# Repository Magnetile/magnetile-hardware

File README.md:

<div align="center">

# Magnetile Hardware

**Open source modular wireless macropad system**

</div>

---

Magnetile is a modular wireless input device. A central hub connects to interchangeable input tiles - mechanical keys, rotary encoders, sliders, display keys - via magnetic pogo pin connectors. The hub presents as a single BLE HID device to the host. Everything is open source.

> **Personal project by a maker in Bavaria, Germany. Not for commercial sale.**

---

## System Overview

Tiles are hot-swappable modules. Each tile has its own small MCU communicating over I²C. The hub aggregates all input and handles the BLE stack. A single LiPo cell in the hub powers the entire system through the pogo pins.

---

## SnapCore Hub Board

The SnapCore is the first hardware in this repository — the nRF52840-based hub PCB.

### Hardware Stack

| Component | Part | Notes |
|-----------|------|-------|
| MCU | Nordic nRF52840 (AQFN-73) | BLE 5, USB, 1MB flash, 256KB RAM |
| LDO | XC6220B331MR-G (Torex, SOT-23-5) | 3.3V, 1A, ~8µA quiescent |
| Battery charger | TP4056 | Single-cell LiPo, ~300mA charge rate |
| USB | USB-C, 5.1kΩ CC pull-downs |  |
| HF crystal | 32 MHz | nRF52840 system clock |
| RTC crystal | 32.768 kHz | Low-power RTC |
| QSPI flash | W25Q128 (16 MB) | Planned for rev 2 |
| Antenna | PCB trace (meander) | SWRA117D reference, tunable RF matching |
| Tile bus | I²C with 4.7kΩ pull-ups | Pogo pin connector |

### PCB Stackup

| Layer | Function |
|-------|----------|
| F.Cu | Components + signals |
| In1.Cu | Solid GND plane |
| In2.Cu | Power distribution + overflow signals |
| B.Cu | Signals |

- Copper pour excluded from antenna area

### Pinout

---

## Tile Architecture

Tiles are designed to be cheap and simple. The hub owns the BLE stack; tiles just report their input state over I²C when polled.

**Tile MCU target:** CH32V003 (RISC-V, I²C slave)

Each tile exposes:
- I²C slave address (configurable per tile type)
- Input state register (key states, encoder delta, slider position)
- Optional: small display framebuffer via I²C (for display tiles)

The pogo pin connector carries: `VCC`, `GND`, `SDA`, `SCL`, and an optional `INT` line for event-driven wake.

Full tile specification in [`docs/connector-pinout.md`](docs/Pinout.svg).

---

## Software

Firmware lives in the companion repository: [magnetile-firmware](https://github.com/magnetile/magnetile-firmware)

| Component | Stack |
|-----------|-------|
| RTOS | Zephyr / Nordic NCS |
| BLE profile | HID over GATT |
| Wireless config | Web Bluetooth API (browser-based) |
| Debug | RTT (Segger J-Link / nRF9160 DK) |
| Hub–tile protocol | I²C polling, CH32V003 slave firmware |

---

## Status

| Milestone | Status |
|-----------|--------|
| Schematic rev 1 | ✅ Complete |
| PCB layout rev 1 | ✅ Complete |
| Fab files (JLCPCB) | 🔄 In progress |
| Rev 1 bring-up | ⏳ Pending |
| Tile hardware | ⏳ Rev 2 |
| Firmware (hub) | 🔄 In progress |
| Tile firmware | ⏳ Rev 2 |
| Web config UI | ⏳ Planned |

---

## Building / Ordering

All design files are in KiCad 9. Fab outputs (Gerbers, BOM, CPL) for JLCPCB are in `snapcore/fab/`.

**Preferred suppliers:** JLCPCB (PCB + assembly), LCSC (components).

This project is designed around JLCPCB's manufacturing ecosystem. If you want to replicate the build, the Gerbers and BOM are ready to upload directly:

[**Order PCBs / PCBA from JLCPCB**](https://jlcpcb.com/?from=mnt)

For managing orders across services - PCB fabrication, assembly, 3D printing, CNC - JLCPCB offers **JLCONE**, a unified desktop platform that consolidates their full manufacturing stack (JLCPCB, JLC3DP, JLCCNC, JLCMC) into one interface. You can upload files, place orders, and track shipments across all services in one place. The desktop version includes a coupon bundle covering various services and shipping.

[**Download JLCONE**](https://jlcpcb.com/download?from=mnt)

---

## Acknowledgements

This project's prototype run is supported by **[JLCPCB](https://jlcpcb.com/?from=mnt)**. Their PCB fabrication and SMT assembly service makes iterating on dense, complex boards like the SnapCore genuinely accessible for independent open source hardware projects.

---

## License

MIT - see [`LICENSE`](LICENSE).

---

## Contributing

This is a personal project in active development. Issues and suggestions are welcome. See [`CONTRIBUTING.md`](CONTRIBUTING.md) before opening a pull request.

---

<div align="center">
<sub>Made in Bavaria · nRF52840 · KiCad · Zephyr</sub>
</div>

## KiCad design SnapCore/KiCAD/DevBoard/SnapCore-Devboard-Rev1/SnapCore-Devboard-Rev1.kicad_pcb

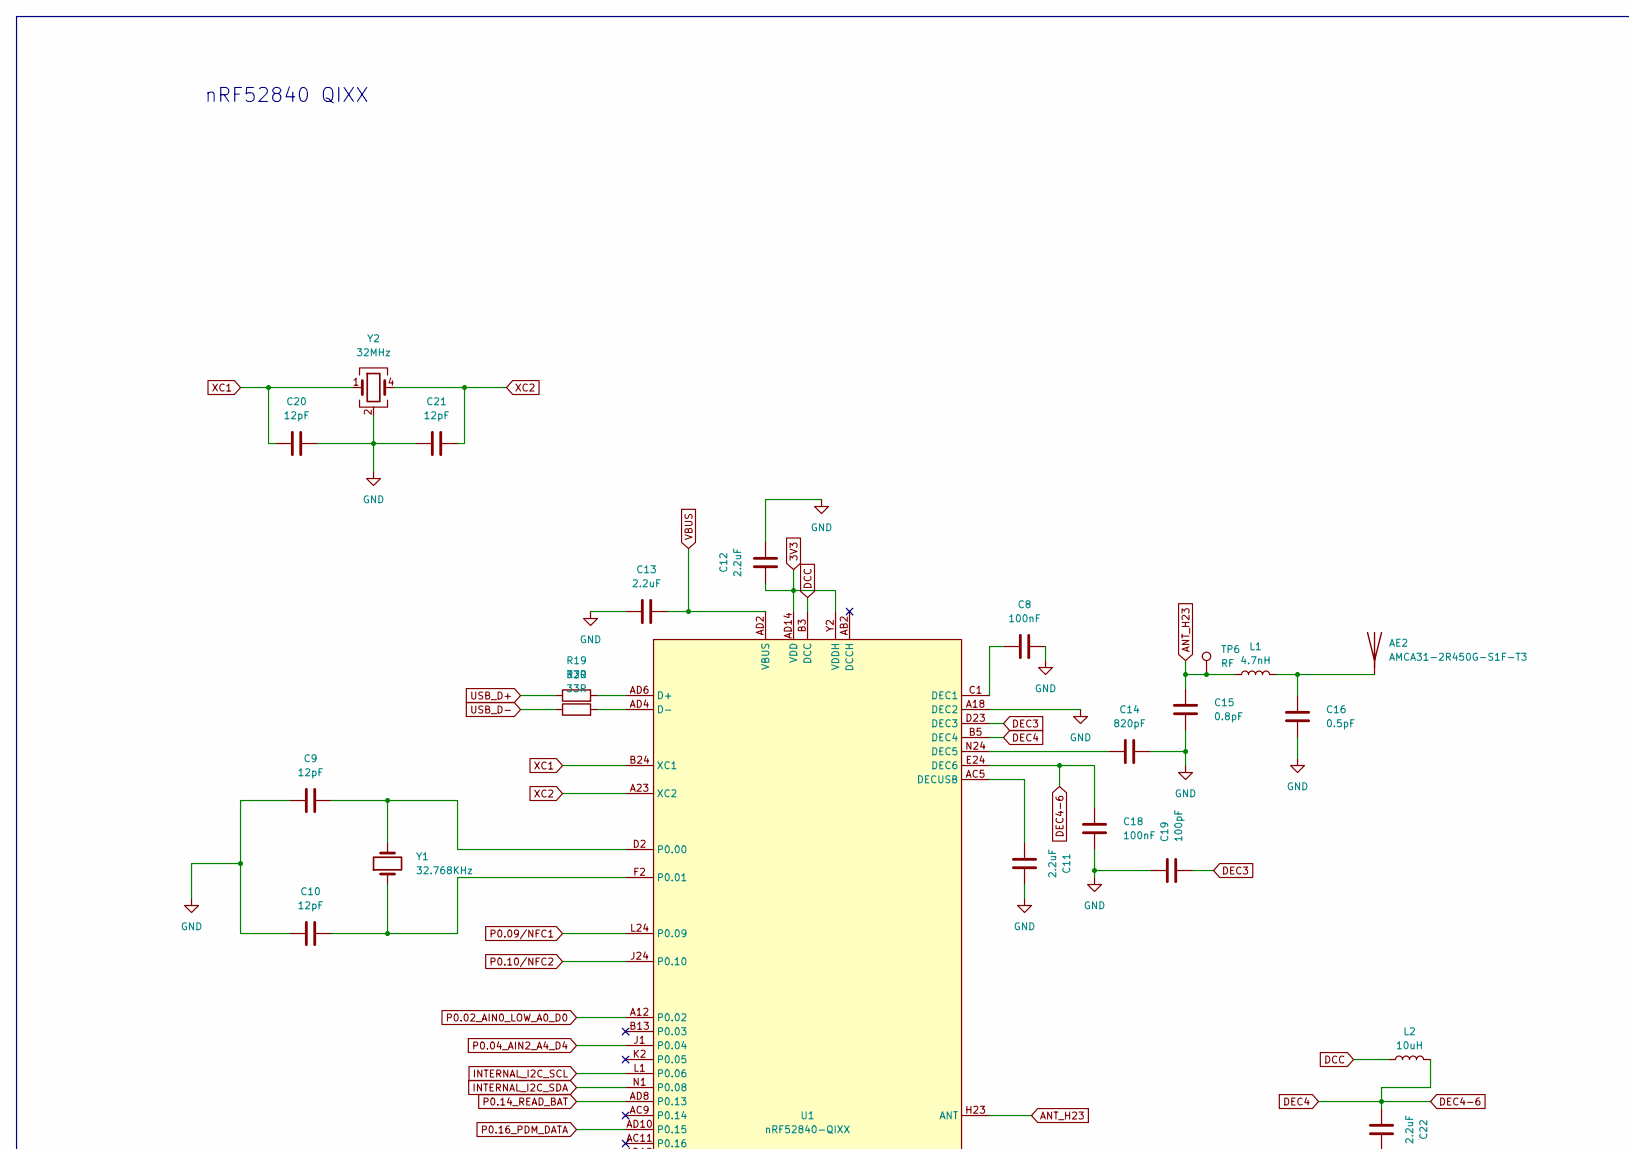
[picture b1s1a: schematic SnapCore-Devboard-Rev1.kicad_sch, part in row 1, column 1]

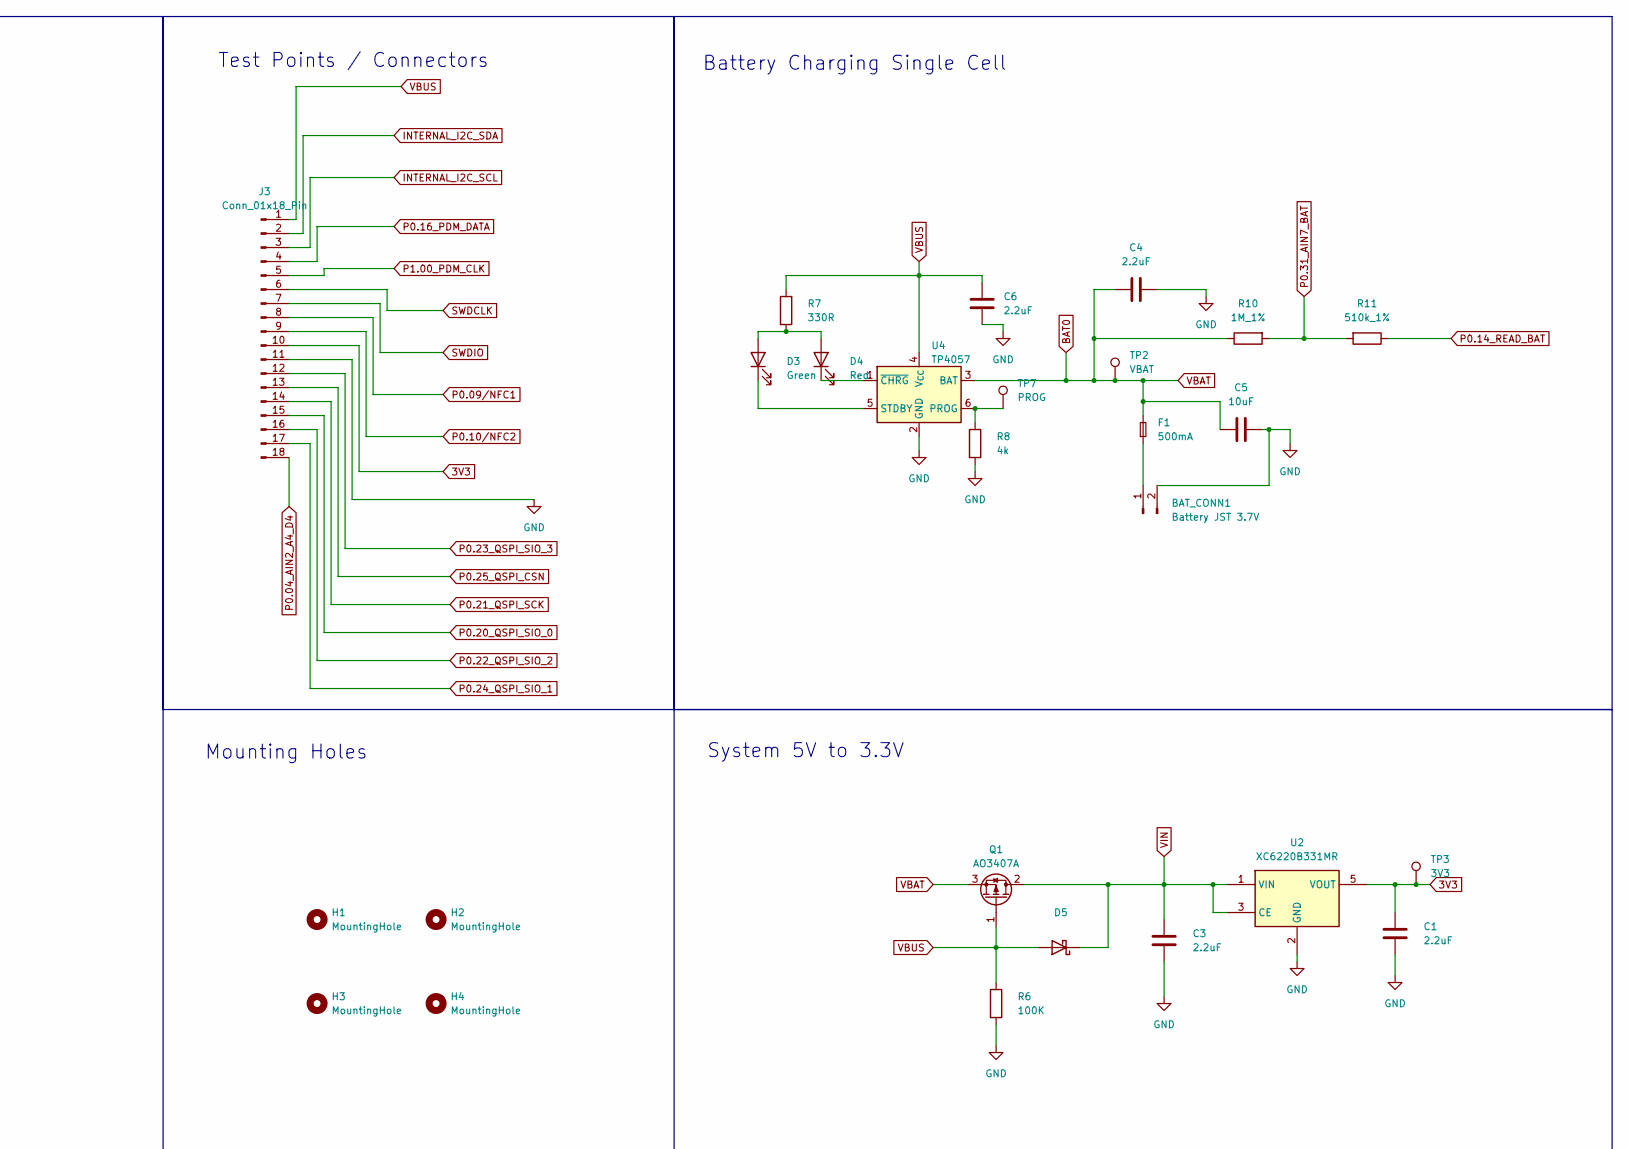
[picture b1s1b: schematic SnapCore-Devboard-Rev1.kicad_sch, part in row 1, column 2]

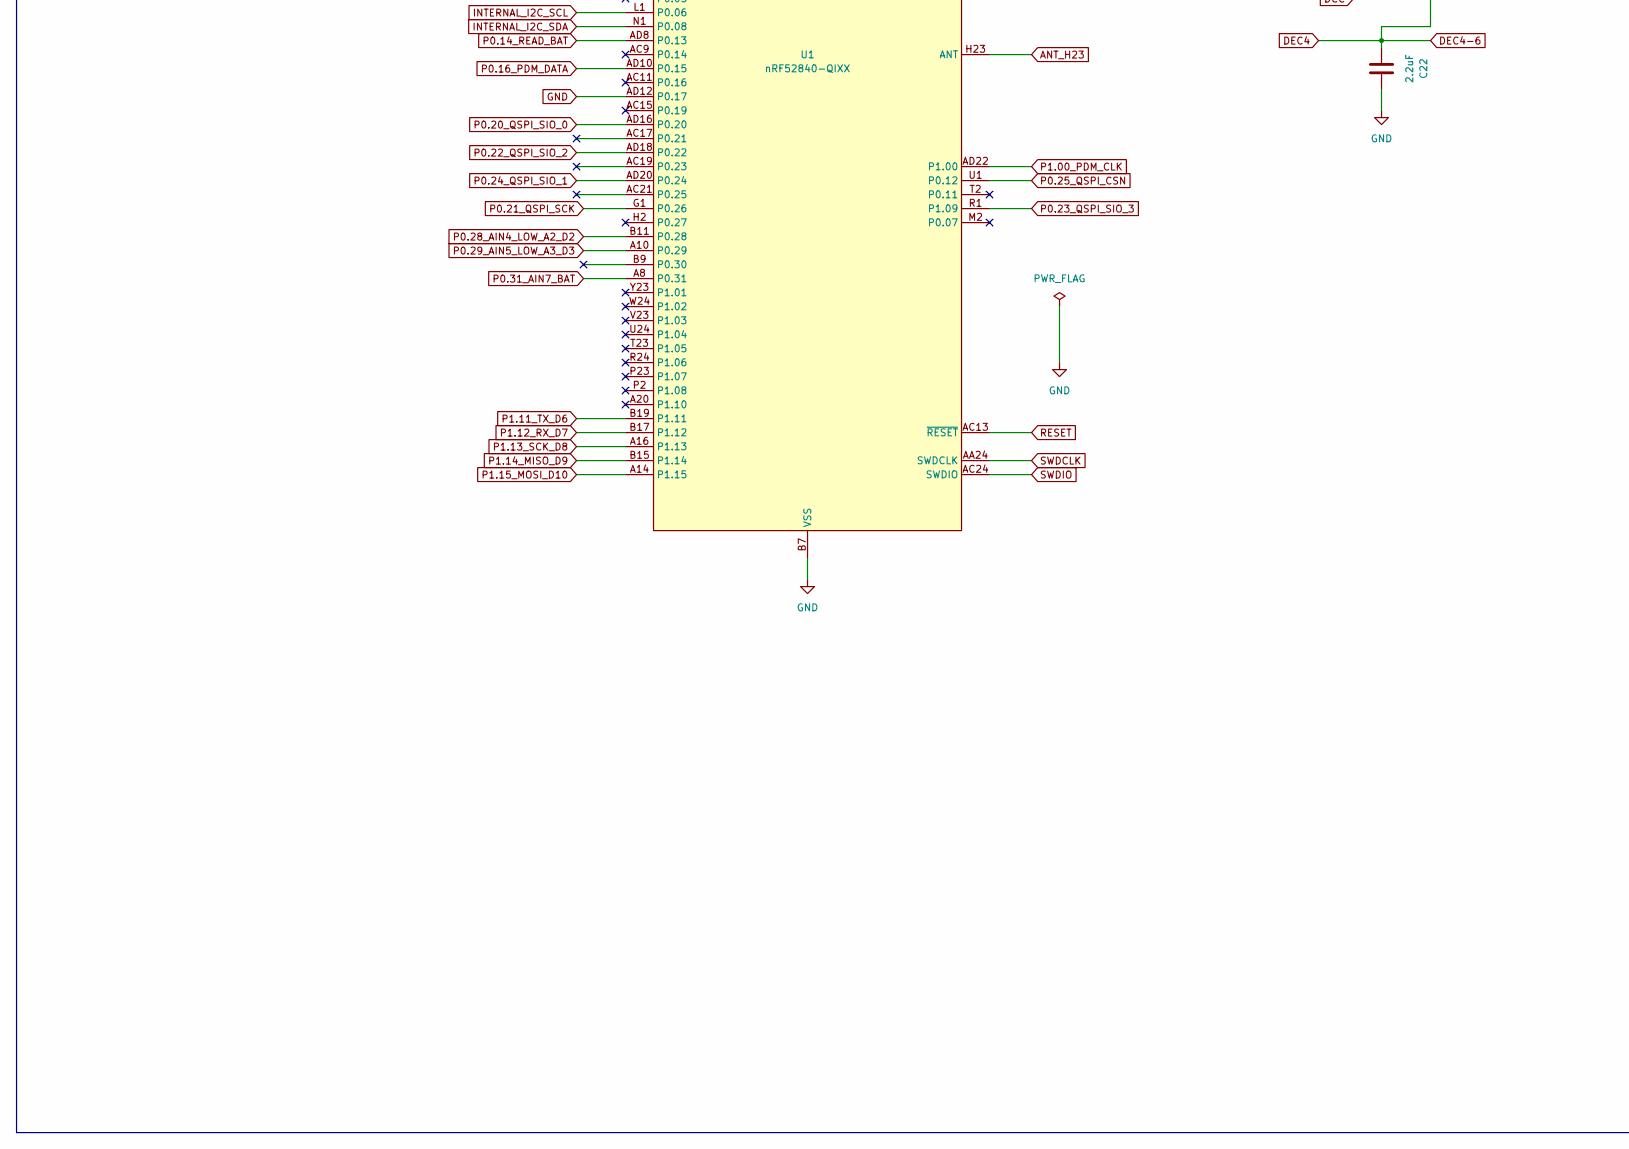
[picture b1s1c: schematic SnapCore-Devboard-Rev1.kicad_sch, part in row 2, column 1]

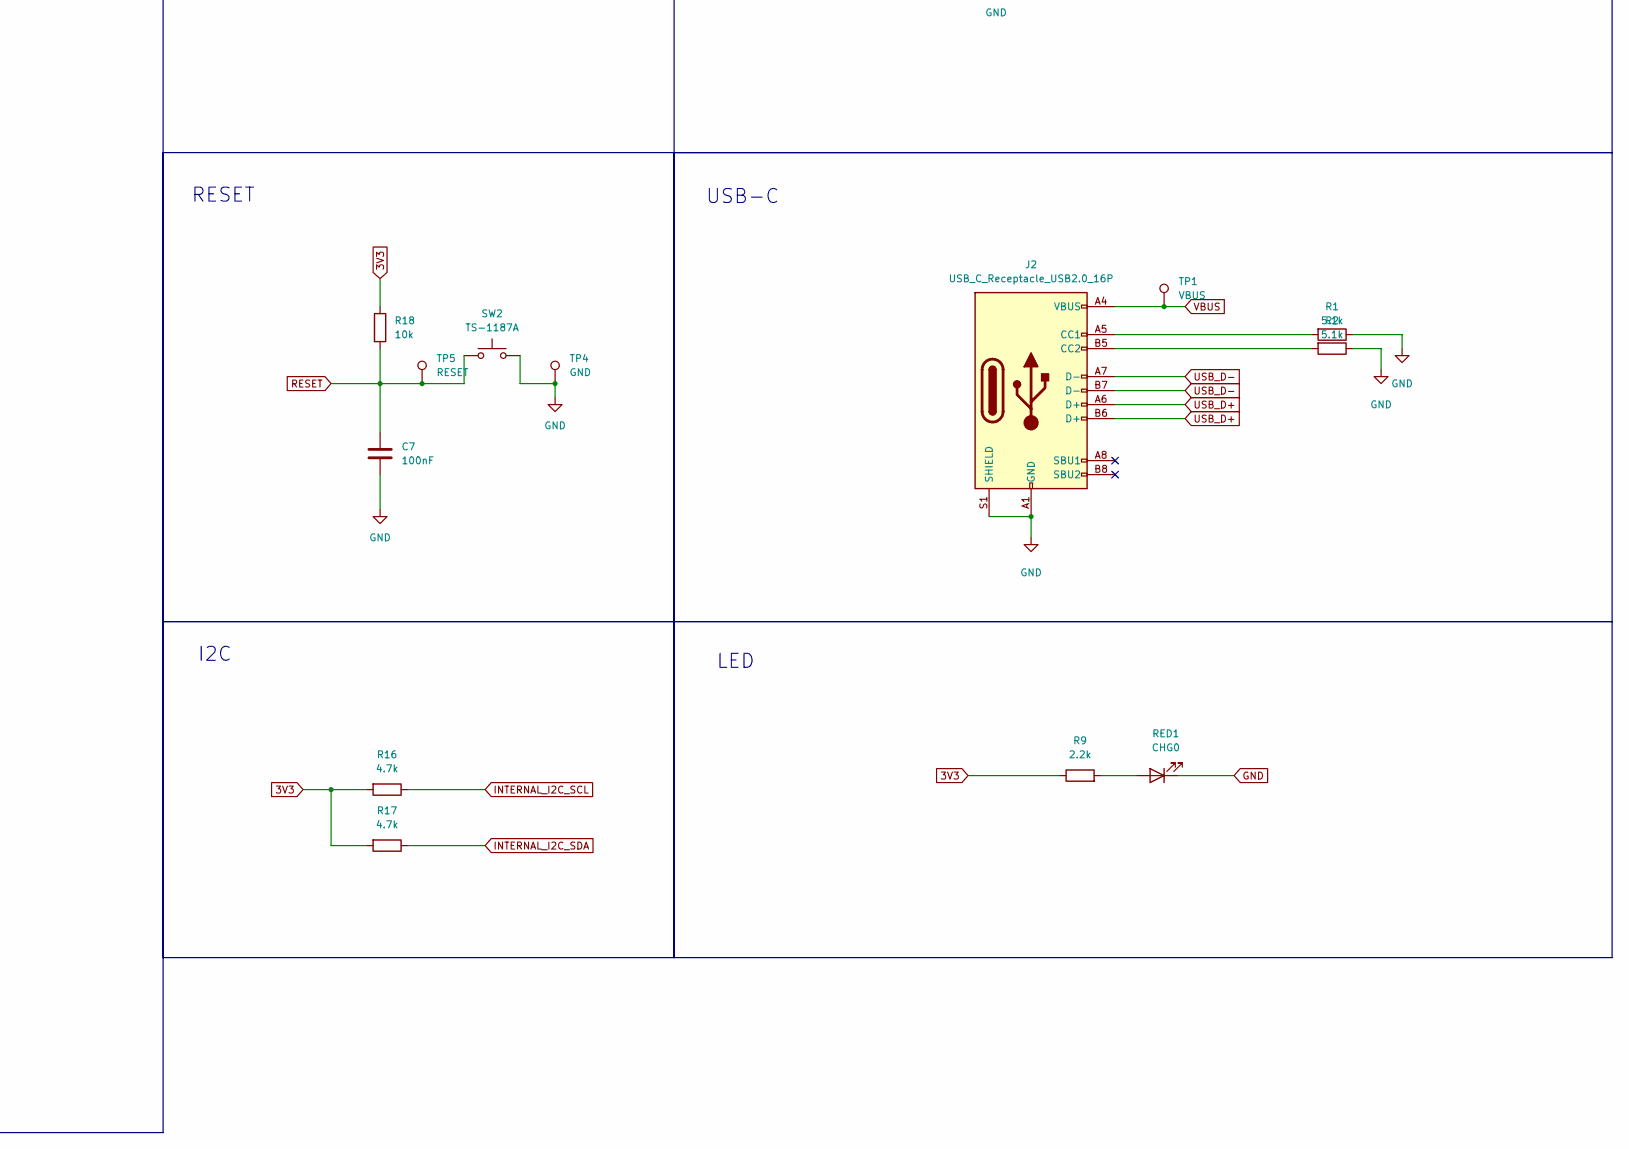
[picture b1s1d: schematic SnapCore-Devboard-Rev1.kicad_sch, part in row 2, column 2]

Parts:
AE2: AMCA31-2R450G-S1F-T3; XDCR_AMCA31-2R450G-S1F-T3
BAT_CONN1: Battery JST 3.7V; JST_EH_B2B-EH-A_1x02_P2.50mm_Vertical
C1, C3, C13, C22: 2.2uF; C_0402_1005Metric
C4: 2.2uF; C_0805_2012Metric
C5: 10uF; C_0402_1005Metric
C6, C11, C12: 2.2uF; C_0603_1608Metric
C7: 100nF; C_0805_2012Metric
C8: 100nF; C_0402_1005Metric
C9, C10, C20, C21: 12pF; C_0402_1005Metric
C14: 820pF; C_0402_1005Metric
C15: 0.8pF; C_0402_1005Metric
C16: 0.5pF; C_0402_1005Metric
C18: 100nF; C_0603_1608Metric
C19: 100pF; C_0402_1005Metric
D3: Green; LED_0805_2012Metric
D4: Red; LED_0805_2012Metric
D5: SDM20U40-7, 40V;250mA; D_SOD-523
F1: 500mA; Fuse_1206_3216Metric
H1, H2, H3, H4: MountingHole; MountingHole_2.2mm_M2_ISO7380_Pad
J2: USB_C_Receptacle_USB2.0_16P; USB_C_Receptacle_GCT_USB4105-xx-A_16P_TopMnt_Horizontal
J3: Conn_01x18_Pin; PinHeader_1x18_P1.27mm_Vertical
L1: 4.7nH; L_0402_1005Metric
L2: 10uH; L_0402_1005Metric
Q1: AO3407A; SOT-23
R1, R2: 5.1k; R_0402_1005Metric
R6: 100K; R_0402_1005Metric
R7: 330R; R_0603_1608Metric
R8: 4k; R_0603_1608Metric
R9: 2.2k; R_0402_1005Metric
R10: 1M_1%; R_0603_1608Metric
R11: 510k_1%; R_0603_1608Metric
R16, R17: 4.7k; R_0402_1005Metric
R18: 10k; R_0402_1005Metric
R19, R20: 33R; R_0402_1005Metric
RED1: CHG0; LED_0603_1608Metric
SW2: TS-1187A; SW_Push_1P1T_XKB_TS-1187A
TP1: VBUS; TestPoint_Pad_D2.0mm
TP2: VBAT; TestPoint_Pad_D2.0mm
TP3: 3V3; TestPoint_Pad_D2.0mm
TP4: GND; TestPoint_Pad_D2.0mm
TP5: RESET; TestPoint_Pad_D2.0mm
TP6: RF; TestPoint_Pad_D2.0mm
TP7: PROG; TestPoint_Pad_D2.0mm
U1: nRF52840-QIXX; Nordic_AQFN-73-1EP_7x7mm_P0.5mm
U2: XC6220B331MR; SOT-23-5
U4: TP4057; TSOT-23-6
Y1: 32.768KHz; Crystal_SMD_3215-2Pin_3.2x1.5mm
Y2: 32MHz; Crystal_SMD_2016-4Pin_2.0x1.6mm

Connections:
3V3: C1.1, C12.2, J3.10, R9.1, R16.2, R17.2, R18.1, TP3.1, U1.A22 (VDD), U1.AD14 (VDD), U1.AD23 (VDD), U1.B1 (VDD), U1.W1 (VDD), U1.Y2 (VDDH), U2.5 (VOUT)
ANT_H23: C15.1, L1.1, TP6.1, U1.H23 (ANT)
BAT0: C4.1, C5.1, F1.2, Q1.3 (S), R10.1, TP2.1, U4.3 (BAT)
DCC: L2.1, U1.B3 (DCC)
DEC3: C19.2, U1.D23 (DEC3)
DEC4: C18.1, C22.2, L2.2, U1.B5 (DEC4), U1.E24 (DEC6)
GND: BAT_CONN1.2, C1.2, C3.2, C4.2, C5.2, C6.1, C7.1, C8.1, C9.2, C10.2, C11.1, C12.1, C13.1, C14.1, C15.2, C16.2, C18.2, C19.1, C20.1, C21.1, C22.1, J2.A1 (GND), J2.A12 (GND), J2.B1 (GND), J2.B12 (GND), J2.S1 (SHIELD), J3.11, R1.1, R2.1, R6.2, R8.2, RED1.1 (K), SW2.2, TP4.1, U1.A18 (DEC2), U1.AD12 (P0.17), U1.B7 (VSS), U1.EP (VSS), U1.F23 (VSS_PA), U2.2 (GND), U4.2 (GND), Y2.2 (G), Y2.3 (G); also elsewhere on the board
INTERNAL_I2C_SCL: J3.3, R16.1, U1.L1 (P0.06)
INTERNAL_I2C_SDA: J3.2, R17.1, U1.N1 (P0.08)
unnamed: AE2.1 (A), C16.1, L1.2
unnamed 10: BAT_CONN1.1, F1.1; also elsewhere on the board
unnamed: D3.2 (A), D4.2 (A), R7.2
unnamed: D3.1 (K), U4.5 (STDBY)
unnamed: D4.1 (K), U4.1 (~CHRG)
unnamed: J2.A5 (CC1), R1.2
unnamed: J2.B5 (CC2), R2.2
unnamed: R9.2, RED1.2 (A)
unnamed: R19.2, U1.AD6 (D+)
unnamed: R20.2, U1.AD4 (D-)
unnamed: C8.2, U1.C1 (DEC1)
unnamed: C14.2, U1.N24 (DEC5)
unnamed: C11.2, U1.AC5 (DECUSB)
unnamed: C9.1, U1.D2 (P0.00), Y1.2
unnamed: C10.1, U1.F2 (P0.01), Y1.1
unnamed: R8.1, TP7.1, U4.6 (PROG)
P0.02_AIN0_LOW_A0_D0: U1.A12 (P0.02)
P0.04_AIN2_A4_D4: J3.18, U1.J1 (P0.04)
P0.09/NFC1: J3.8, U1.L24 (P0.09)
P0.10/NFC2: J3.9, U1.J24 (P0.10)
P0.14_READ_BAT: R11.1, U1.AD8 (P0.13)
P0.16_PDM_DATA: J3.4, U1.AD10 (P0.15)
P0.20_QSPI_SIO_0: J3.15, U1.AD16 (P0.20)
P0.21_QSPI_SCK: J3.14, U1.G1 (P0.26)
P0.22_QSPI_SIO_2: J3.16, U1.AD18 (P0.22)
P0.23_QSPI_SIO_3: J3.12, U1.R1 (P1.09)
P0.24_QSPI_SIO_1: J3.17, U1.AD20 (P0.24)
P0.25_QSPI_CSN: J3.13, U1.U1 (P0.12)
P0.28_AIN4_LOW_A2_D2: U1.B11 (P0.28)
P0.29_AIN5_LOW_A3_D3: U1.A10 (P0.29)
P0.31_AIN7_BAT: R10.2, R11.2, U1.A8 (P0.31)
P1.00_PDM_CLK: J3.5, U1.AD22 (P1.00)
P1.11_TX_D6: U1.B19 (P1.11)
P1.12_RX_D7: U1.B17 (P1.12)
P1.13_SCK_D8: U1.A16 (P1.13)
P1.14_MISO_D9: U1.B15 (P1.14)
P1.15_MOSI_D10: U1.A14 (P1.15)
RESET: C7.2, R18.2, SW2.1, TP5.1, U1.AC13 (~RESET)
SWDCLK: J3.6, U1.AA24 (SWDCLK)
SWDIO: J3.7, U1.AC24 (SWDIO)
USB_D+: J2.A6 (D+), J2.B6 (D+), R19.1
USB_D-: J2.A7 (D-), J2.B7 (D-), R20.1
VBUS: C6.2, C13.2, D5.2 (A), J2.A4 (VBUS), J2.A9 (VBUS), J2.B4 (VBUS), J2.B9 (VBUS), J3.1, Q1.1 (G), R6.1, R7.1, TP1.1, U1.AD2 (VBUS), U4.4 (V_{CC})
VIN: C3.1, D5.1 (K), Q1.2 (D), U2.1 (VIN), U2.3 (CE)
XC1: C20.2, U1.B24 (XC1), Y2.1
XC2: C21.2, U1.A23 (XC2), Y2.4

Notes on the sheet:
USB-C
Test Points / Connectors
LED
Mounting Holes
RESET
I2C
Battery Charging Single Cell
System 5V to 3.3V
nRF52840 QIXX

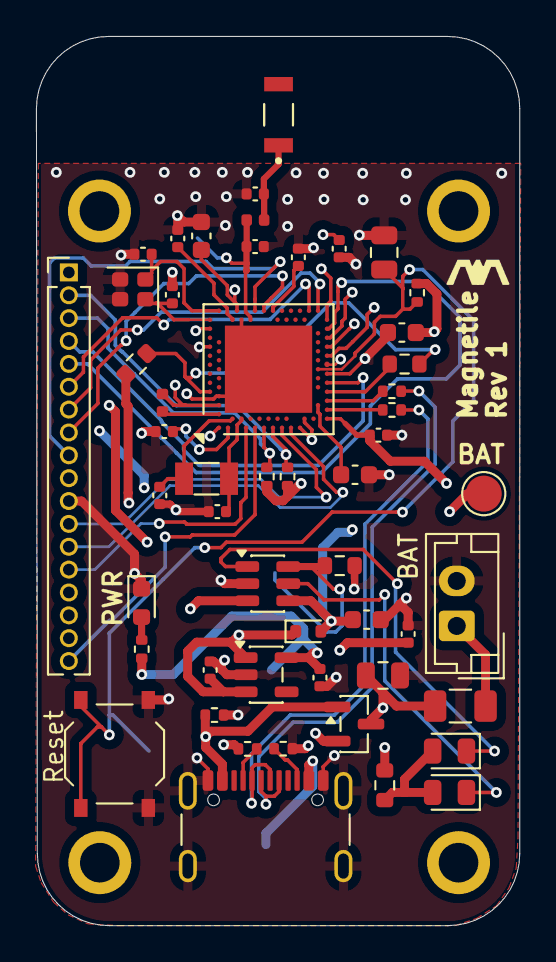
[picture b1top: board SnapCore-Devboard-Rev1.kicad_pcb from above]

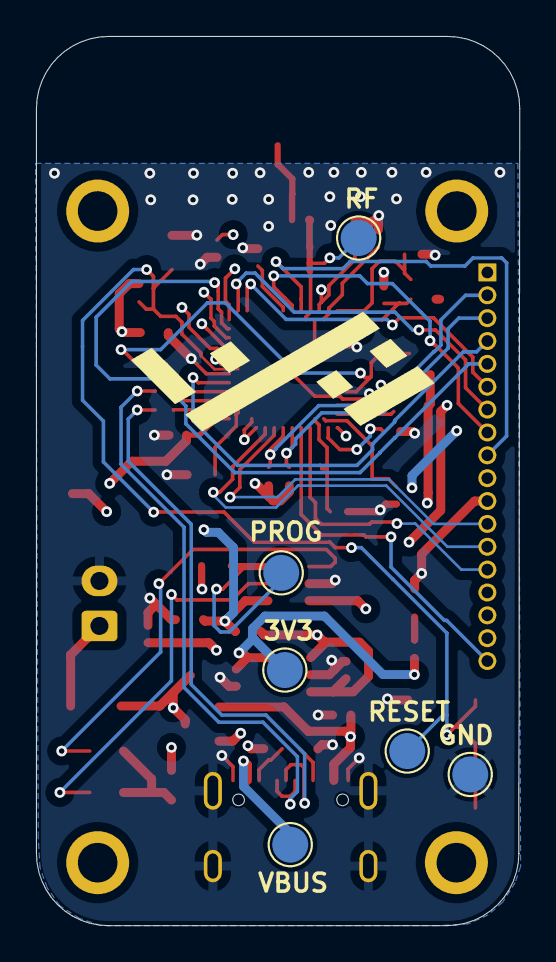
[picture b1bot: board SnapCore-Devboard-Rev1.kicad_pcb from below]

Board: 4 copper layers, 26.8 x 49.4 mm, 62 parts (6 on the bottom side), 47 nets.

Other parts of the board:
BAT: Battery JST 3.7V; JST_EH_B2B-EH-A_1x02_P2.50mm_Vertical

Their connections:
GND: BAT.2; also elsewhere on the board
unnamed 10: BAT.1; also elsewhere on the board

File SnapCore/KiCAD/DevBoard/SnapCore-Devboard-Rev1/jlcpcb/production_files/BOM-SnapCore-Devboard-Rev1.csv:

Comment,Designator,Footprint,LCSC,Quantity
100K,R6,R_0402_1005Metric,C25741,1
100nF,C18,C_0603_1608Metric,C14663,1
100nF,C8,C_0402_1005Metric,C1525,1
100nF,C7,C_0805_2012Metric,C49678,1
100pF,C19,C_0402_1005Metric,C1546,1
10k,R18,R_0402_1005Metric,C25744,1
10uF,C5,C_0402_1005Metric,C15525,1
10uH,L2,L_0402_1005Metric,C48946156,1
12pF,"C10,C20,C21,C9",C_0402_1005Metric,C1547,4
1M_1%,R10,R_0603_1608Metric,C22935,1
2.2k,R9,R_0402_1005Metric,C25879,1
2.2uF,"C1,C13,C22,C3",C_0402_1005Metric,C12530,4
2.2uF,"C11,C12,C6",C_0603_1608Metric,C23630,3
2.2uF,C4,C_0805_2012Metric,C377773,1
32.768KHz,Y1,Crystal_SMD_3215-2Pin_3.2x1.5mm,C32346,1
32MHz,Y2,Crystal_SMD_2016-4Pin_2.0x1.6mm,C187794,1
330R,R7,R_0603_1608Metric,C23138,1
33R,"R19,R20",R_0402_1005Metric,C25105,2
4.7k,"R16,R17",R_0402_1005Metric,C25900,2
4.7nH,L1,L_0402_1005Metric,C13595,1
4k,R8,R_0603_1608Metric,C23018,1
5.1k,"R1,R2",R_0402_1005Metric,C25905,2
500mA,F1,Fuse_1206_3216Metric,C20798,1
510k_1%,R11,R_0603_1608Metric,C23192,1
820pF,C14,C_0402_1005Metric,C1523,1
AMCA31-2R450G-S1F-T3,AE2,XDCR_AMCA31-2R450G-S1F-T3,C3283994,1
AO3407A,Q1,SOT-23,C15155,1
CHG0,RED1,LED_0603_1608Metric,C2286,1
Green,D3,LED_0805_2012Metric,C2297,1
Red,D4,LED_0805_2012Metric,C84256,1
"SDM20U40-7, 40V;250mA",D5,D_SOD-523,C139439,1
TP4057,U4,TSOT-23-6,C440390,1
TS-1187A,SW2,SW_Push_1P1T_XKB_TS-1187A,C318884,1
USB_C_Receptacle_USB2.0_16P,J2,USB_C_Receptacle_GCT_USB4105-xx-A_16P_TopMnt_Horizontal,C136423,1
XC6220B331MR,U2,SOT-23-5,C3040644,1
nRF52840-QIXX,U1,Nordic_AQFN-73-1EP_7x7mm_P0.5mm,C190794,1
Conn_01x18_Pin,J3,PinHeader_1x18_P1.27mm_Vertical,,1
PROG,TP7,TestPoint_Pad_D2.0mm,,1
RF,TP6,TestPoint_Pad_D2.0mm,,1
RESET,TP5,TestPoint_Pad_D2.0mm,,1
GND,TP4,TestPoint_Pad_D2.0mm,,1
3V3,TP3,TestPoint_Pad_D2.0mm,,1
VBAT,TP2,TestPoint_Pad_D2.0mm,,1
VBUS,TP1,TestPoint_Pad_D2.0mm,,1
Battery JST 3.7V,BAT,JST_EH_B2B-EH-A_1x02_P2.50mm_Vertical,,1

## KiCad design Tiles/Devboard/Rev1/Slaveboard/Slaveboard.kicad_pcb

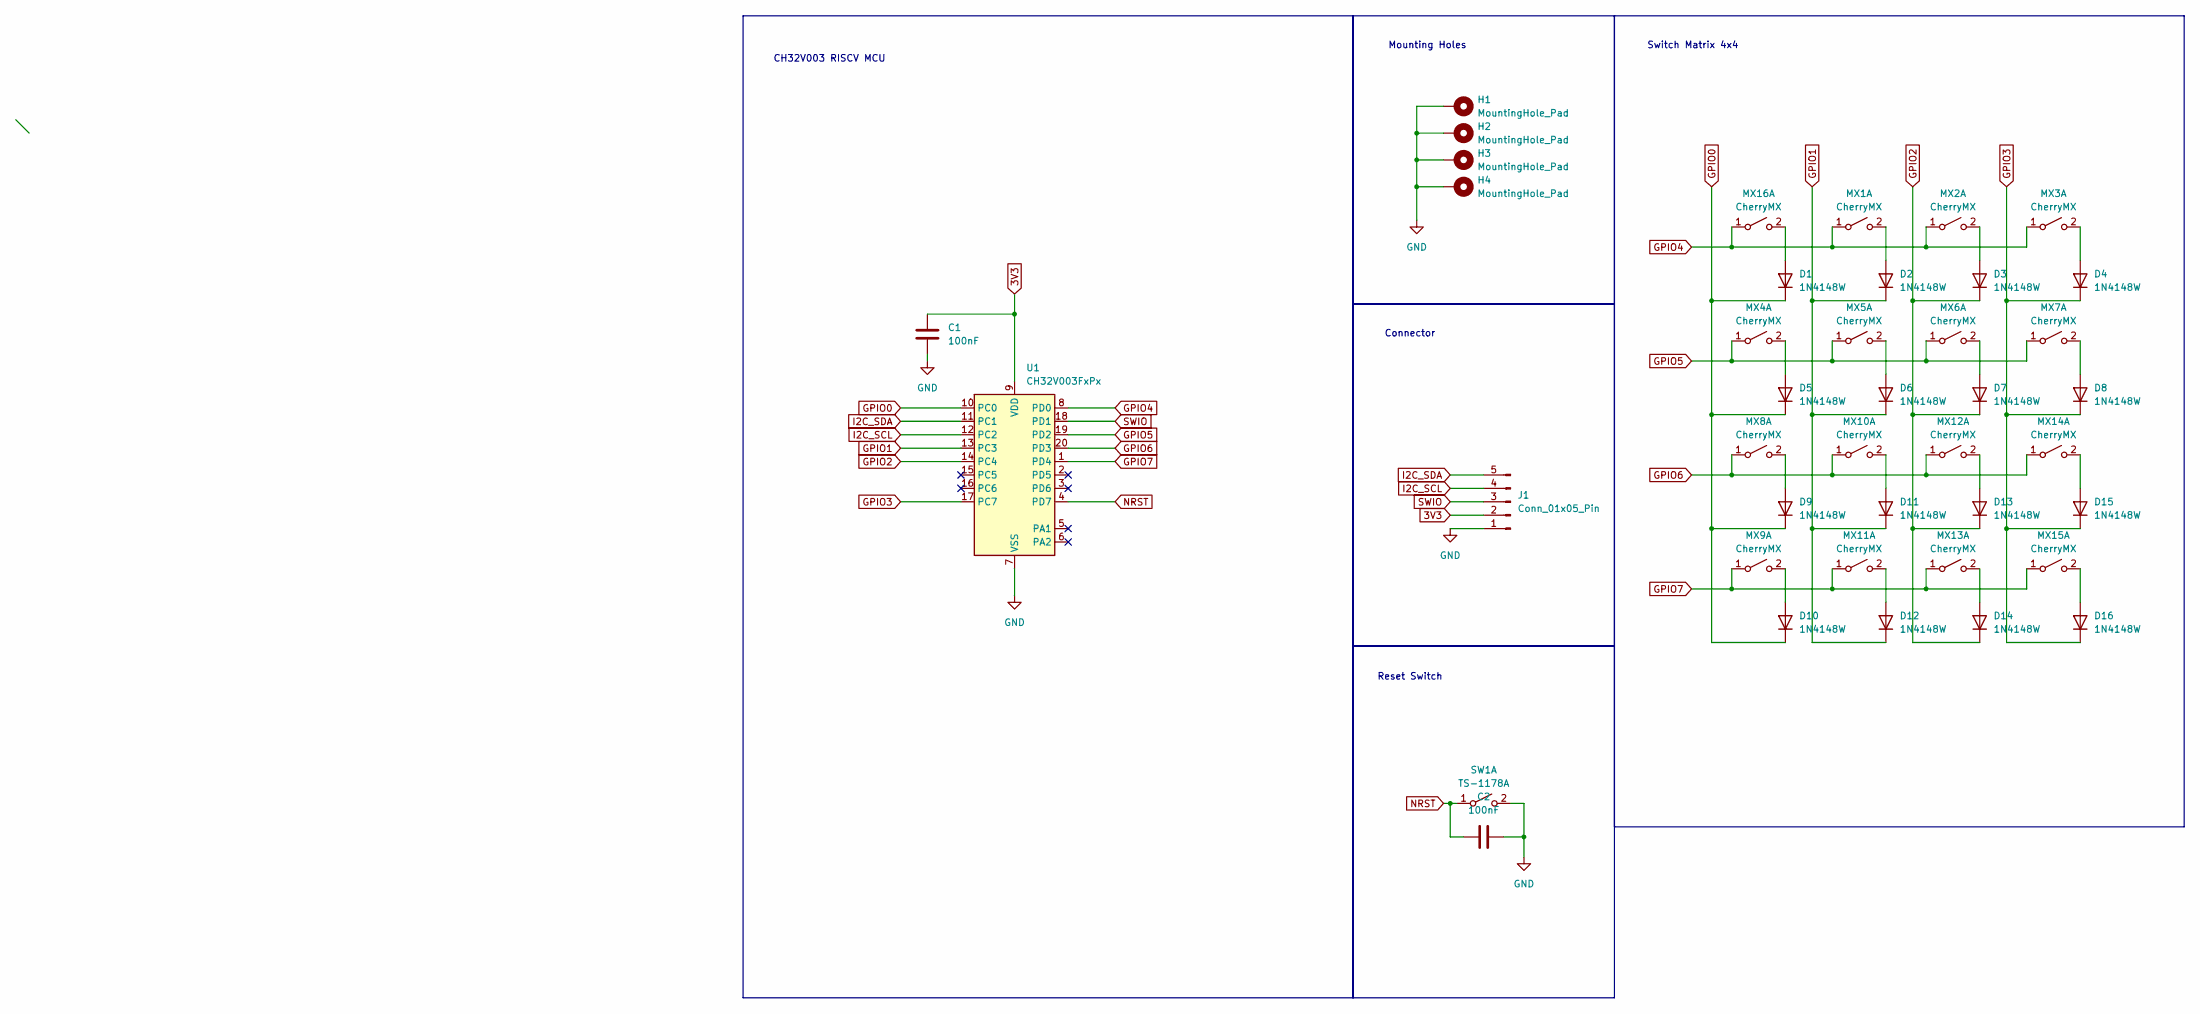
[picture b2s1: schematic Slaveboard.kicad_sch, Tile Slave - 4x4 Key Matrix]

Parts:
C1, C2: 100nF; C_0603_1608Metric
D1, D2, D3, D4, D5, D6, D7, D8, D9, D10, D11, D12, D13, D14, D15, D16: 1N4148W; D_SOD-123
H1, H2, H3, H4: MountingHole_Pad; MountingHole_2.2mm_M2_DIN965_Pad
J1: Conn_01x05_Pin; PinHeader_1x05_P1.27mm_Vertical
MX1, MX2, MX3, MX4, MX5, MX6, MX7, MX8, MX9, MX10, MX11, MX12, MX13, MX14, MX15, MX16: CherryMX; SW_Cherry_MX_1.00u_PCB
SW1: TS-1178A; SW_Push_1P1T_XKB_TS-1187A
U1: CH32V003FxPx; TSSOP-20_4.4x6.5mm_P0.65mm

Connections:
3V3: C1.1, J1.2, U1.9 (VDD)
GND: C1.2, C2.2, H1.1, H2.1, H3.1, H4.1, J1.1, SW1.2 (B), U1.7 (VSS); also elsewhere on the board
GPIO0: D1.1 (K), D5.1 (K), D9.1 (K), D10.1 (K), U1.10 (PC0)
GPIO1: D2.1 (K), D6.1 (K), D11.1 (K), D12.1 (K), U1.13 (PC3)
GPIO2: D3.1 (K), D7.1 (K), D13.1 (K), D14.1 (K), U1.14 (PC4)
GPIO3: D4.1 (K), D8.1 (K), D15.1 (K), D16.1 (K), U1.17 (PC7)
GPIO4: MX1.1 (A), MX2.1 (A), MX3.1 (A), MX16.1 (A), U1.8 (PD0)
GPIO5: MX4.1 (A), MX5.1 (A), MX6.1 (A), MX7.1 (A), U1.19 (PD2)
GPIO6: MX8.1 (A), MX10.1 (A), MX12.1 (A), MX14.1 (A), U1.20 (PD3)
GPIO7: MX9.1 (A), MX11.1 (A), MX13.1 (A), MX15.1 (A), U1.1 (PD4)
I2C_SCL: J1.4, U1.12 (PC2)
I2C_SDA: J1.5, U1.11 (PC1)
NRST: C2.1, SW1.1 (A), U1.4 (PD7); also elsewhere on the board
unnamed: D1.2 (A), MX16.2 (B)
unnamed: D2.2 (A), MX1.2 (B)
unnamed: D3.2 (A), MX2.2 (B)
unnamed: D4.2 (A), MX3.2 (B)
unnamed: D5.2 (A), MX4.2 (B)
unnamed: D6.2 (A), MX5.2 (B)
unnamed: D7.2 (A), MX6.2 (B)
unnamed: D8.2 (A), MX7.2 (B)
unnamed: D9.2 (A), MX8.2 (B)
unnamed: D10.2 (A), MX9.2 (B)
unnamed: D11.2 (A), MX10.2 (B)
unnamed: D12.2 (A), MX11.2 (B)
unnamed: D13.2 (A), MX12.2 (B)
unnamed: D14.2 (A), MX13.2 (B)
unnamed: D15.2 (A), MX14.2 (B)
unnamed: D16.2 (A), MX15.2 (B)
SWIO: J1.3, U1.18 (PD1)

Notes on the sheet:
Reset Switch
CH32V003 RISCV MCU
Mounting Holes
Connector
Switch Matrix 4x4

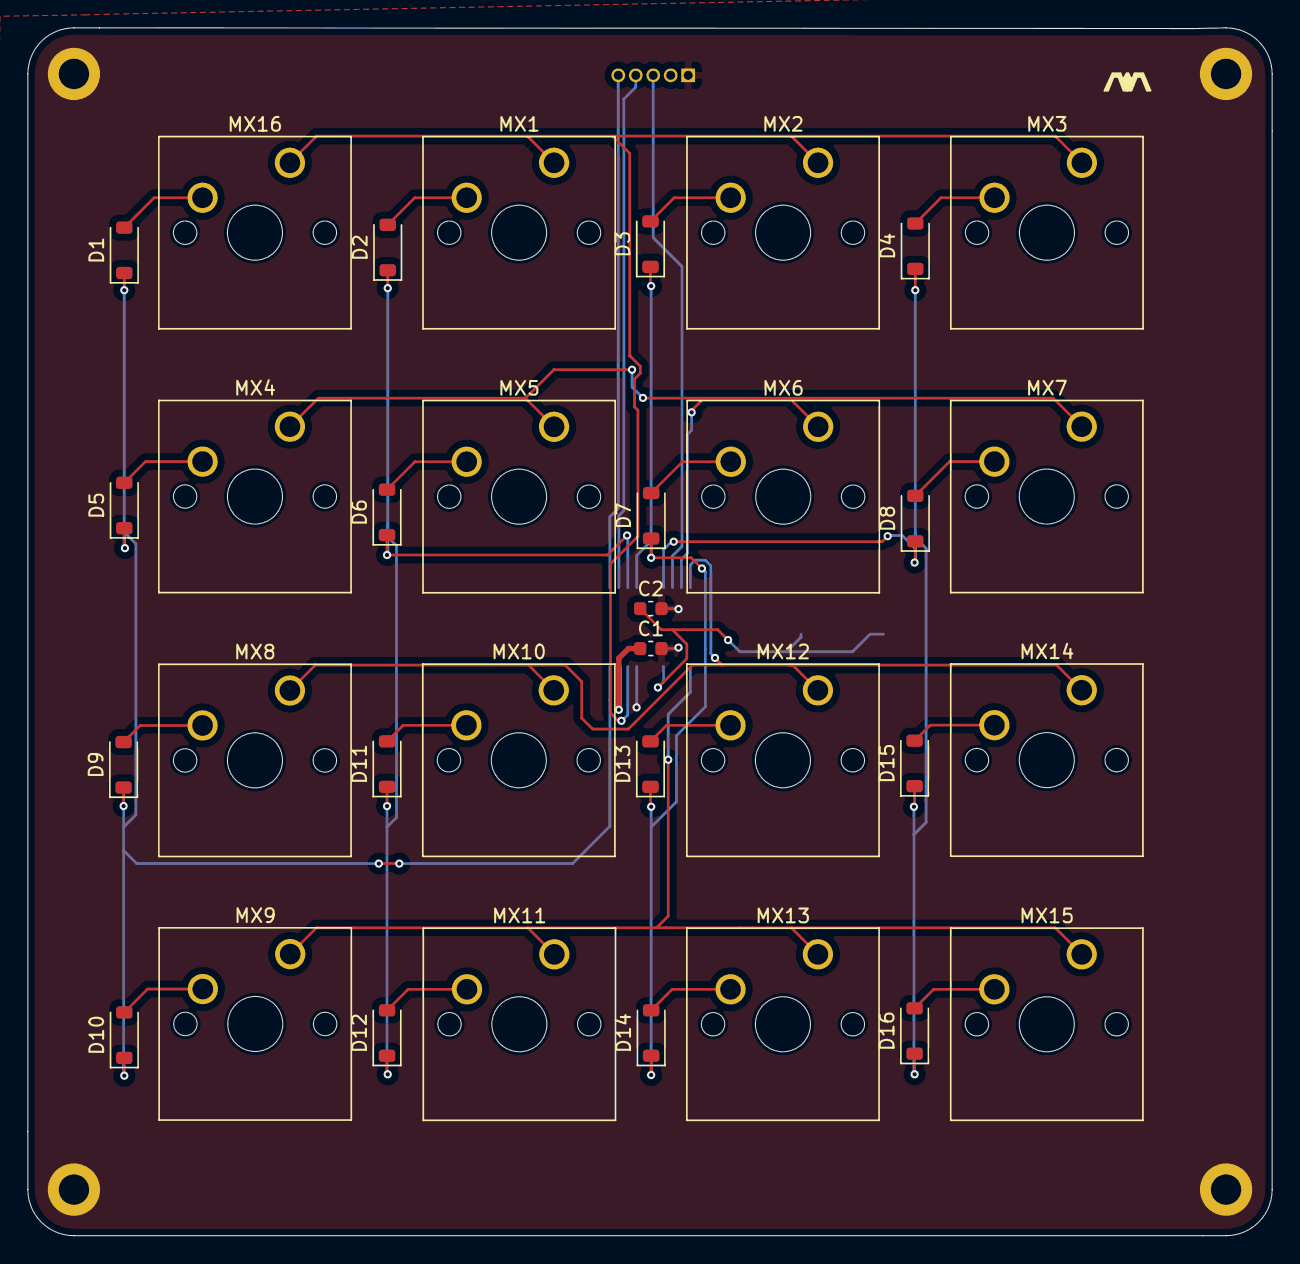
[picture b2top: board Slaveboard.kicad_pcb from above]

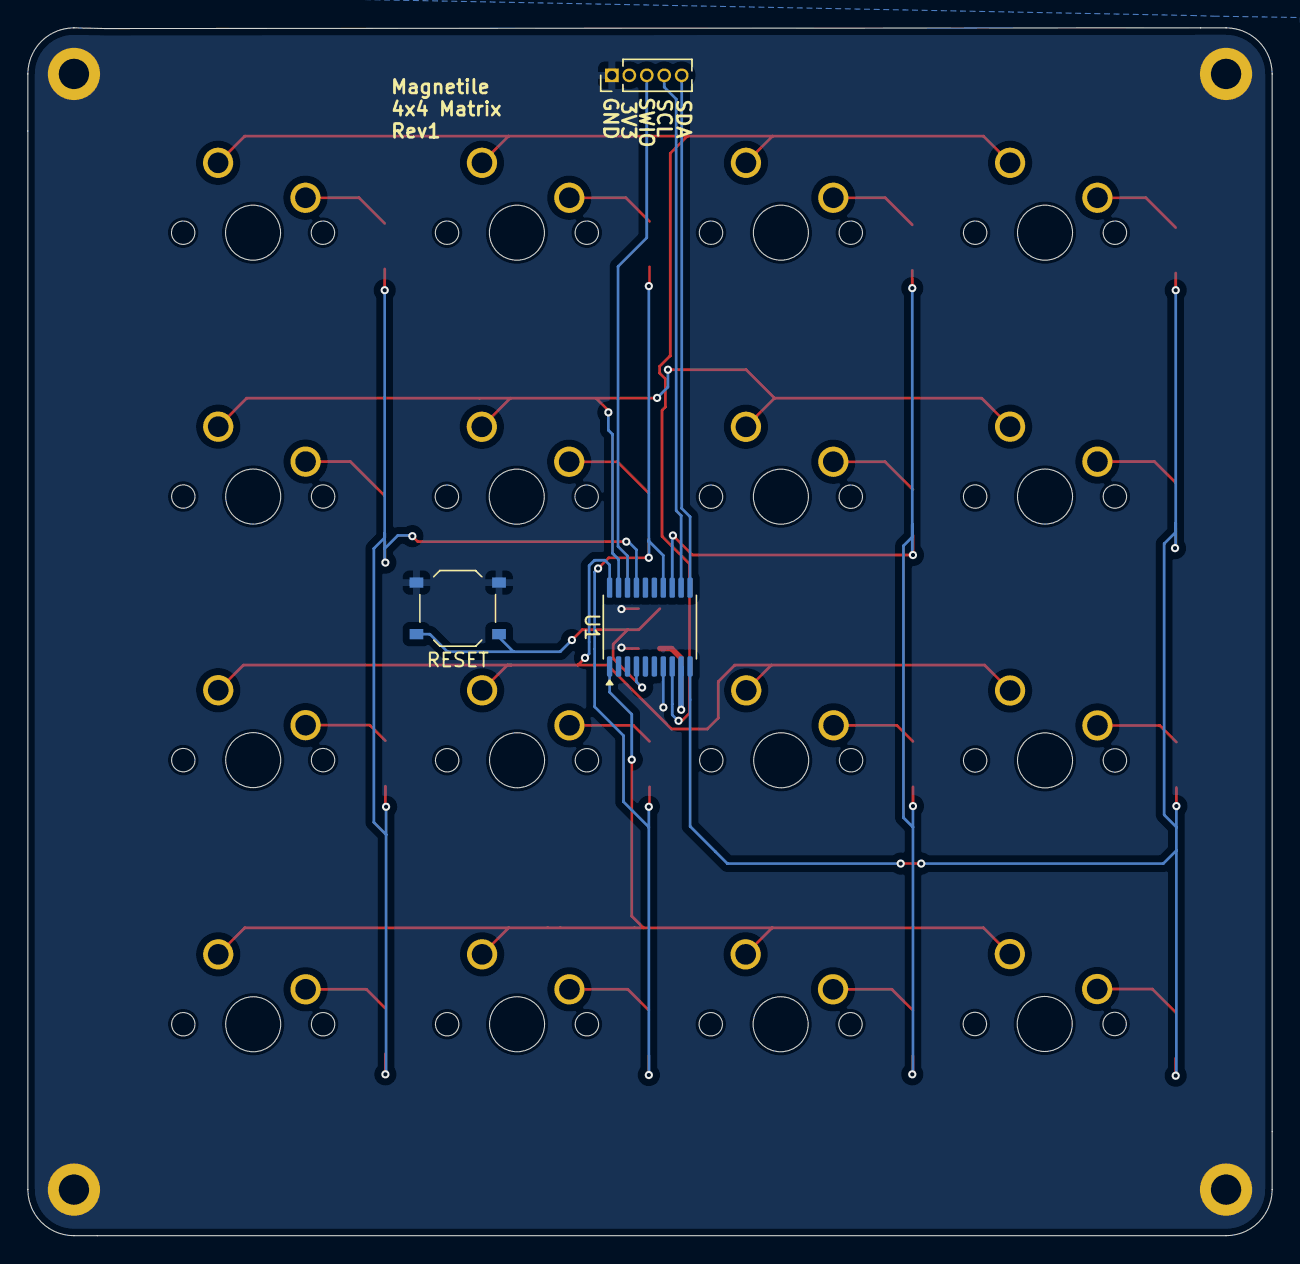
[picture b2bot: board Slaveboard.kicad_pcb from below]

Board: 4 copper layers, 90.5 x 87.8 mm, 41 parts (3 on the bottom side), 30 nets.

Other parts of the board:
RESET: TS-1178A; SW_Push_1P1T_XKB_TS-1187A

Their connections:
GND: RESET.2 (B); also elsewhere on the board
NRST: RESET.1 (A); also elsewhere on the board

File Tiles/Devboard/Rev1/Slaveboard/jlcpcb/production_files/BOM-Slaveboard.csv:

Comment,Designator,Footprint,LCSC,Quantity
100nF,"C1,C2",C_0603_1608Metric,C14663,2
1N4148W,"D1,D10,D11,D12,D13,D14,D15,D16,D2,D3,D4,D5,D6,D7,D8,D9",D_SOD-123,C81598,16
CH32V003FxPx,U1,TSSOP-20_4.4x6.5mm_P0.65mm,C5187096,1
TS-1178A,RESET,SW_Push_1P1T_XKB_TS-1187A,C318884,1

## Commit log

2026-03-16 Init
    Added Overview diagram
    Added Logo
2026-03-16 Update README with project details and status
    Added detailed project description, system overview, hardware stack, and status updates.
2026-03-16 Added SnapCore Rev1 Devboard files
2026-03-16 Added gitignore file
    To stop adding DS_Store
2026-03-16 Added KiCad Files
2026-03-16 KiCAD Files Update
2026-03-16 Final added Kicad Files
2026-03-16 Added Pinout diagram
2026-03-17 Updated gitignore
2026-03-17 Updated Pinout diagram
2026-03-20 Added first revision of a tile devboard
    Based on CH32V003F4P6 MCU
2026-03-20 Added Silkscreen QoL
2026-03-20 Updated Production files
2026-03-22 Smaller Update
2026-03-22 Updated Devboard to use Chip Antenna instead of PCB Antenna for easier RF matching
2026-03-22 Removed unecessary silkscreen, Fixed small layout issue
2026-03-22 Add pinout section to README
    Added pinout section with diagram to README.
2026-03-23 Tried implementing AS5600 on the board
    Added schematic
    Need to rework layout first to integrate properly (or use breakout board instead)
2026-03-25 Switched to TP4057 Charger IC, Added J4 to bottom pinout
2026-03-25 Fixed trace for pwr led being too small
2026-03-27 Final Rev1 fix before ordering
    Fixed Y2 not having correct pinout
    Made pcb antenna smaller to have it closer to the edge of the board
    Final routing adjustments
    Adjusted RF matching circuit
2026-03-27 Update license from CERN-OHL-S to MIT and added JLCPCB
